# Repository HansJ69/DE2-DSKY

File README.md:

# DE2-DSKY

**8. Apollo DSKY console maquette**: maketa ovládacího rozhraní DSKY z kosmické lodi Apollo.

## O DSKY

**DSKY** (Display and Keyboard) bylo uživatelské rozhraní palubního počítače **Apollo Guidance Computer (AGC)**, vyvinutého v MIT Instrumentation Laboratory. Prostřednictvím DSKY komunikovali astronauti s počítačem během letů na Měsíc.

### Co DSKY umožňovalo

- zadávat příkazy a data do počítače,
- kontrolovat stav lodi,
- počítat korekce dráhy,
- řídit motory,
- provádět astronomickou navigaci.

### Systém VERB a NOUN

Místo textového nebo grafického rozhraní se používal jednoduchý dvojslovný systém:

- **VERB** (sloveso) určuje, *jakou akci* provést,
- **NOUN** (podstatné jméno) určuje, *čeho se akce týká*.

Příklad: `VERB 16 NOUN 36` znamená "průběžně zobrazuj čas počítače".

### Displej a kontrolky

Údaje se zobrazovaly na elektroluminiscenčním displeji, který ukazoval číselné hodnoty ve třech řádcích (registry R1, R2, R3) a kódy programu, VERB a NOUN. Součástí panelu byla také sada stavových kontrolek, například:

- `COMP ACTY` (počítač právě pracuje),
- `PROG` (chyba programu),
- `OPR ERR` (chyba obsluhy),
- `GIMBAL LOCK` (blokace kardanového závěsu).

## O projektu

Cílem projektu je co nejvěrněji napodobit rozhraní **DSKY** z Apolla. Maketa je postavená na **Raspberry Pi Pico** a **vlastní desce plošných spojů (PCB)**.

### Funkce

- Zadávání příkazů systémem **VERB / NOUN** stejně jako v Apolu.
- Několik původních kombinací VERB a NOUN, například zobrazení času.
- Čtení dat z **GPS** a **IMU** přes vlastní VERB/NOUN kódy.
- Vlastní příkazy nad rámec originálu.

### Autentičnost

- **Klávesnice:** mechanické spínače pro odpovídající hmat a zvuk tlačítek.
- **Displej:** místo hotových displejů jsou segmenty tvořeny jednotlivými LED diodami, nad kterými je tvarovaný difuzér. Ten světlo rozptýlí a vytvoří tvar sedmisegmentové číslice. Barva a vzhled se tak co nejvíc blíží původnímu elektroluminiscenčnímu displeji.
- **Kontrolky:** stavové indikátory (původně žárovičky v oknech kontrolek) jsou na panelu ve stejném uspořádání jako na originále.

### Multiplexování

Aby se ušetřily piny Pica, je většina periferií řízena **multiplexně**:

- **Klávesnice** je zapojena jako maticová (řádky a sloupce).
- **LED segmenty displeje** jsou ovládány multiplexem, kdy se jednotlivé číslice rychle střídají.
- **Kontrolky** jsou ve vlastní multiplexní matici.

## Schéma

### Blokové schéma obvodu

## Hardware

### Kusovník (BOM)

| Součástka | Funkce v obvodu | Počet | Odkaz / Datasheet |
| :--- | :--- | :--- | :--- |
| **Raspberry Pi Pico (RP2040)** | Hlavní řídicí mikrokontrolér (skenování matice 5×4, řízení shift registrů, 3× PWM pro jas LED, I2C a UART komunikace) | 1 ks | [Raspberry Pi Pico Datasheet (PDF)](https://datasheets.raspberrypi.com/pico/pico-datasheet.pdf) |
| **SCT2024CSTG** | 16kanálový LED driver (posuvný registr s konstantním proudem a pinem `OE` pro PWM stmívání samostatných větví) | X ks *(min. 3 ks)* | [SCT2024 Datasheet (AllDatasheet)](https://www.alldatasheet.com/view.jsp?Searchword=SCT2024) |
| **Keychron K Pro Switch Mint** | Mechanické spínače pro uživatelskou klávesnici zapojenou v matici 5×4 | 20 ks *(1 balení = 110 ks)* | [Alza – Keychron K Pro Switch Mint](https://www.alza.cz/keychron-k-pro-switch-mint-110-pcs-d12749940.htm) |
| **LED diody (displej, alarmy, tlačítka)** | Optická indikace, segmenty displeje a podsvícení kláves | *k doplnění* | *Doplnit dle konkrétních typů* |
| **Step-down modul s LM2596** | Spínaný snižující DC-DC měnič z 20 V (z PD triggeru) na 5 V pro napájení elektroniky a LED | 2–3 ks *(dle odběru)* | [Drátek – Modul LM2596](https://dratek.cz/arduino-platforma/1303-stepdown-nastavitelny-menic-s-lm2596-dc-dc.html) / [TI LM2596 Datasheet (PDF)](https://www.ti.com/lit/ds/symlink/lm2596.pdf) |
| **USB-C PD Trigger Board (20 V)** | Vyjednání 20V napájecího profilu z powerbanky přes USB-C Power Delivery | 1 ks | [HUSB238 / PD Trigger reference](https://www.alldatasheet.com/view.jsp?Searchword=HUSB238) |
| **QMC5883P (modul)** | 3osý magnetometr (digitální kompas), připojený na sběrnici I2C | 1 ks | [QMC5883P Datasheet (AllDatasheet)](https://www.alldatasheet.com/view.jsp?Searchword=QMC5883P) |
| **MPU-6050 (modul)** | 6osý inerciální senzor (3osý akcelerometr + 3osý gyroskop) na sběrnici I2C | 1 ks | [MPU-6050 Datasheet (TDK InvenSense)](https://invensense.tdk.com/wp-content/uploads/2015/02/MPU-6000-Datasheet1.pdf) |
| **GY-213V-TU21D (čip HTU21D)** | Senzor teploty a relativní vlhkosti na sběrnici I2C | 1 ks | [HTU21D Datasheet (AllDatasheet)](https://www.alldatasheet.com/view.jsp?Searchword=HTU21D) |
| **GY-NEO6MV2 (čip u-blox NEO-6M)** | GPS přijímač komunikující přes TTL sériovou linku (UART) | 1 ks | [u-blox NEO-6 Datasheet (AllDatasheet)](https://www.alldatasheet.com/view.jsp?Searchword=NEO-6M) |

## Software

- Jazyk / platforma: MicroPython
- Knihovny: [doplnit]

## Fotky / ukázka

-

## Zdroje a inspirace

- https://github.com/rrainey/DSKY-digital-indicator-replica/tree/master
- https://github.com/Apollo-Replica/DSKY/tree/main
- https://github.com/ManoDaSilva/AGC_DSKY_Replica

## Tým

|Jméno|GitHub|Role|
|-------|--------|------|
| Adam Šimůnek | [@adamsim10](https://github.com/adamsim10) | - |
| Jan Pikner | [@HansJ69](https://github.com/HansJ69) | - |
| Jan Mareš | [@Error-30](https://github.com/Error-30) | - |

## Struktura repozitáře

```
DE2-DSKY/
├── docs/                         # prostor pro dokumentaci (zatím prázdný)
├── models/                       # prostor pro 3D modely (zatím prázdný)
├── pictures/                     # obrázky a schémata použité v README
│   ├── blok_shem_obvodu.png
│   ├── dsky_interface.png
│   └── dsky_interface_diagram.png
├── pcb/                          # návrhy desek v KiCadu
│   ├── led_display/              # deska LED displeje
│   │   ├── DSKY_led_display.kicad_pro
│   │   ├── DSKY_led_display.kicad_sch
│   │   ├── DSKY_led_display.kicad_pcb
│   │   └── DSKY_led_display.pdf
│   ├── lights_keyboard/          # deska kontrolek a klávesnice
│   │   ├── lights_keyboard.kicad_pro
│   │   ├── lights_keyboard.kicad_sch
│   │   ├── lights_keyboard.kicad_pcb
│   │   ├── buttonmatrix.kicad_sch
│   │   ├── external_connections.kicad_sch
│   │   ├── lights.kicad_sch
│   │   └── Gerber Files/         # výrobní data (Gerbery a vrtání)
│   └── main_board/               # hlavní deska
│       ├── main_board.kicad_pro
│       ├── main_board.kicad_sch
│       └── main_board.kicad_pcb
├── src/                          # prostor pro firmware (zatím prázdný)
│   └── .gitkeep
├── LICENSE
└── README.md
```

V podsložkách s PCB jsou také pomocné soubory KiCadu, knihovny a zálohy návrhů. Výrobní data desky klávesnice jsou uložena také jako archiv `Gerber Files.zip`.

## Stav projektu

- [x] Návrh schématu (PCB)
- [x] Výběr součástek
- [x] Návrh PCB
- [ ] BOM
- [x] Schema zapojení (přibližné)
- [ ] Blokové schéma
- [ ] Dokumentace a fotky

## Licence

Projekt je šířen pod licencí GPL-3.0, viz soubor [LICENSE](LICENSE).

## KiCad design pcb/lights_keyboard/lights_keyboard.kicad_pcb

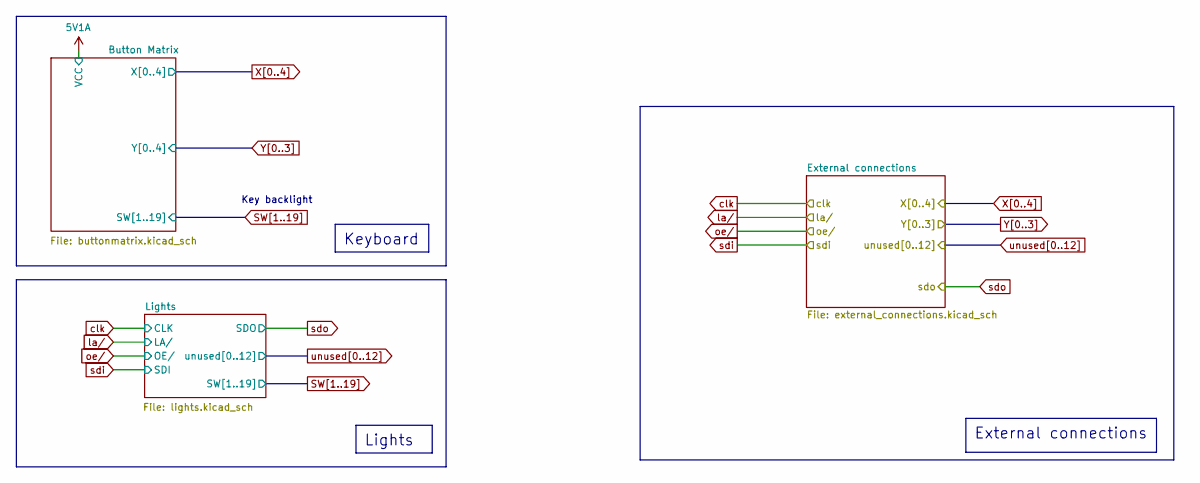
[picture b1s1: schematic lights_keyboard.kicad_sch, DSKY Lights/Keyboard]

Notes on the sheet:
Key backlight
Keyboard
Lights
External connections

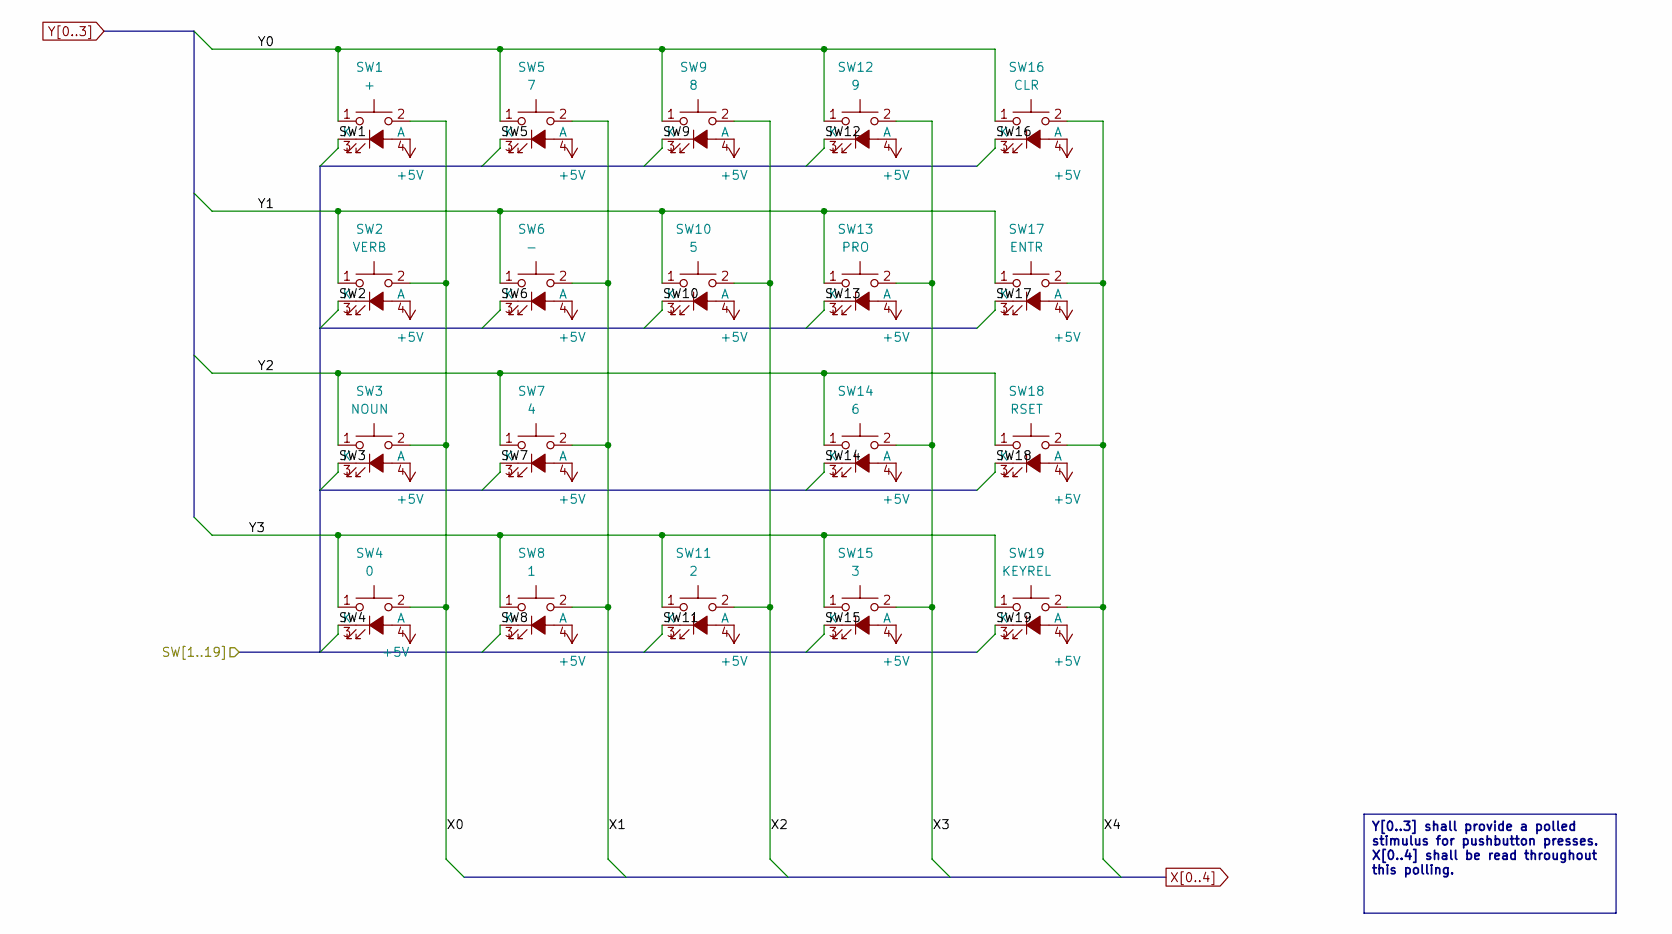
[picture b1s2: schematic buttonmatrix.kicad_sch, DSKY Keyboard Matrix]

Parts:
SW1: +; CherryMX_1.00u_LED
SW2: VERB; CherryMX_1.00u_LED
SW3: NOUN; CherryMX_1.00u_LED
SW4: 0; CherryMX_1.00u_LED
SW5: 7; CherryMX_1.00u_LED
SW6: -; CherryMX_1.00u_LED
SW7: 4; CherryMX_1.00u_LED
SW8: 1; CherryMX_1.00u_LED
SW9: 8; CherryMX_1.00u_LED
SW10: 5; CherryMX_1.00u_LED
SW11: 2; CherryMX_1.00u_LED
SW12: 9; CherryMX_1.00u_LED
SW13: PRO; CherryMX_1.00u_LED
SW14: 6; CherryMX_1.00u_LED
SW15: 3; CherryMX_1.00u_LED
SW16: CLR; CherryMX_1.00u_LED
SW17: ENTR; CherryMX_1.00u_LED
SW18: RSET; CherryMX_1.00u_LED
SW19: KEYREL; CherryMX_1.00u_LED

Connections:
+5V: SW1.4 (A), SW2.4 (A), SW3.4 (A), SW4.4 (A), SW5.4 (A), SW6.4 (A), SW7.4 (A), SW8.4 (A), SW9.4 (A), SW10.4 (A), SW11.4 (A), SW12.4 (A), SW13.4 (A), SW14.4 (A), SW15.4 (A), SW16.4 (A), SW17.4 (A), SW18.4 (A), SW19.4 (A); also elsewhere on the board
SW1: SW1.3 (K); also elsewhere on the board
SW2: SW2.3 (K); also elsewhere on the board
SW3: SW3.3 (K); also elsewhere on the board
SW4: SW4.3 (K); also elsewhere on the board
SW5: SW5.3 (K); also elsewhere on the board
SW6: SW6.3 (K); also elsewhere on the board
SW7: SW7.3 (K); also elsewhere on the board
SW8: SW8.3 (K); also elsewhere on the board
SW9: SW9.3 (K); also elsewhere on the board
SW10: SW10.3 (K); also elsewhere on the board
SW11: SW11.3 (K); also elsewhere on the board
SW12: SW12.3 (K); also elsewhere on the board
SW13: SW13.3 (K); also elsewhere on the board
SW14: SW14.3 (K); also elsewhere on the board
SW15: SW15.3 (K); also elsewhere on the board
SW16: SW16.3 (K); also elsewhere on the board
SW17: SW17.3 (K); also elsewhere on the board
SW18: SW18.3 (K); also elsewhere on the board
SW19: SW19.3 (K); also elsewhere on the board
X0: SW1.2, SW2.2, SW3.2, SW4.2; also elsewhere on the board
X1: SW5.2, SW6.2, SW7.2, SW8.2; also elsewhere on the board
X2: SW9.2, SW10.2, SW11.2; also elsewhere on the board
X3: SW12.2, SW13.2, SW14.2, SW15.2; also elsewhere on the board
X4: SW16.2, SW17.2, SW18.2, SW19.2; also elsewhere on the board
Y0: SW1.1, SW5.1, SW9.1, SW12.1, SW16.1; also elsewhere on the board
Y1: SW2.1, SW6.1, SW10.1, SW13.1, SW17.1; also elsewhere on the board
Y2: SW3.1, SW7.1, SW14.1, SW18.1; also elsewhere on the board
Y3: SW4.1, SW8.1, SW11.1, SW15.1, SW19.1; also elsewhere on the board

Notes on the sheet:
Y[0..3] shall provide a polled stimulus for pushbutton presses. X[0..4] shall be read throughout this polling.

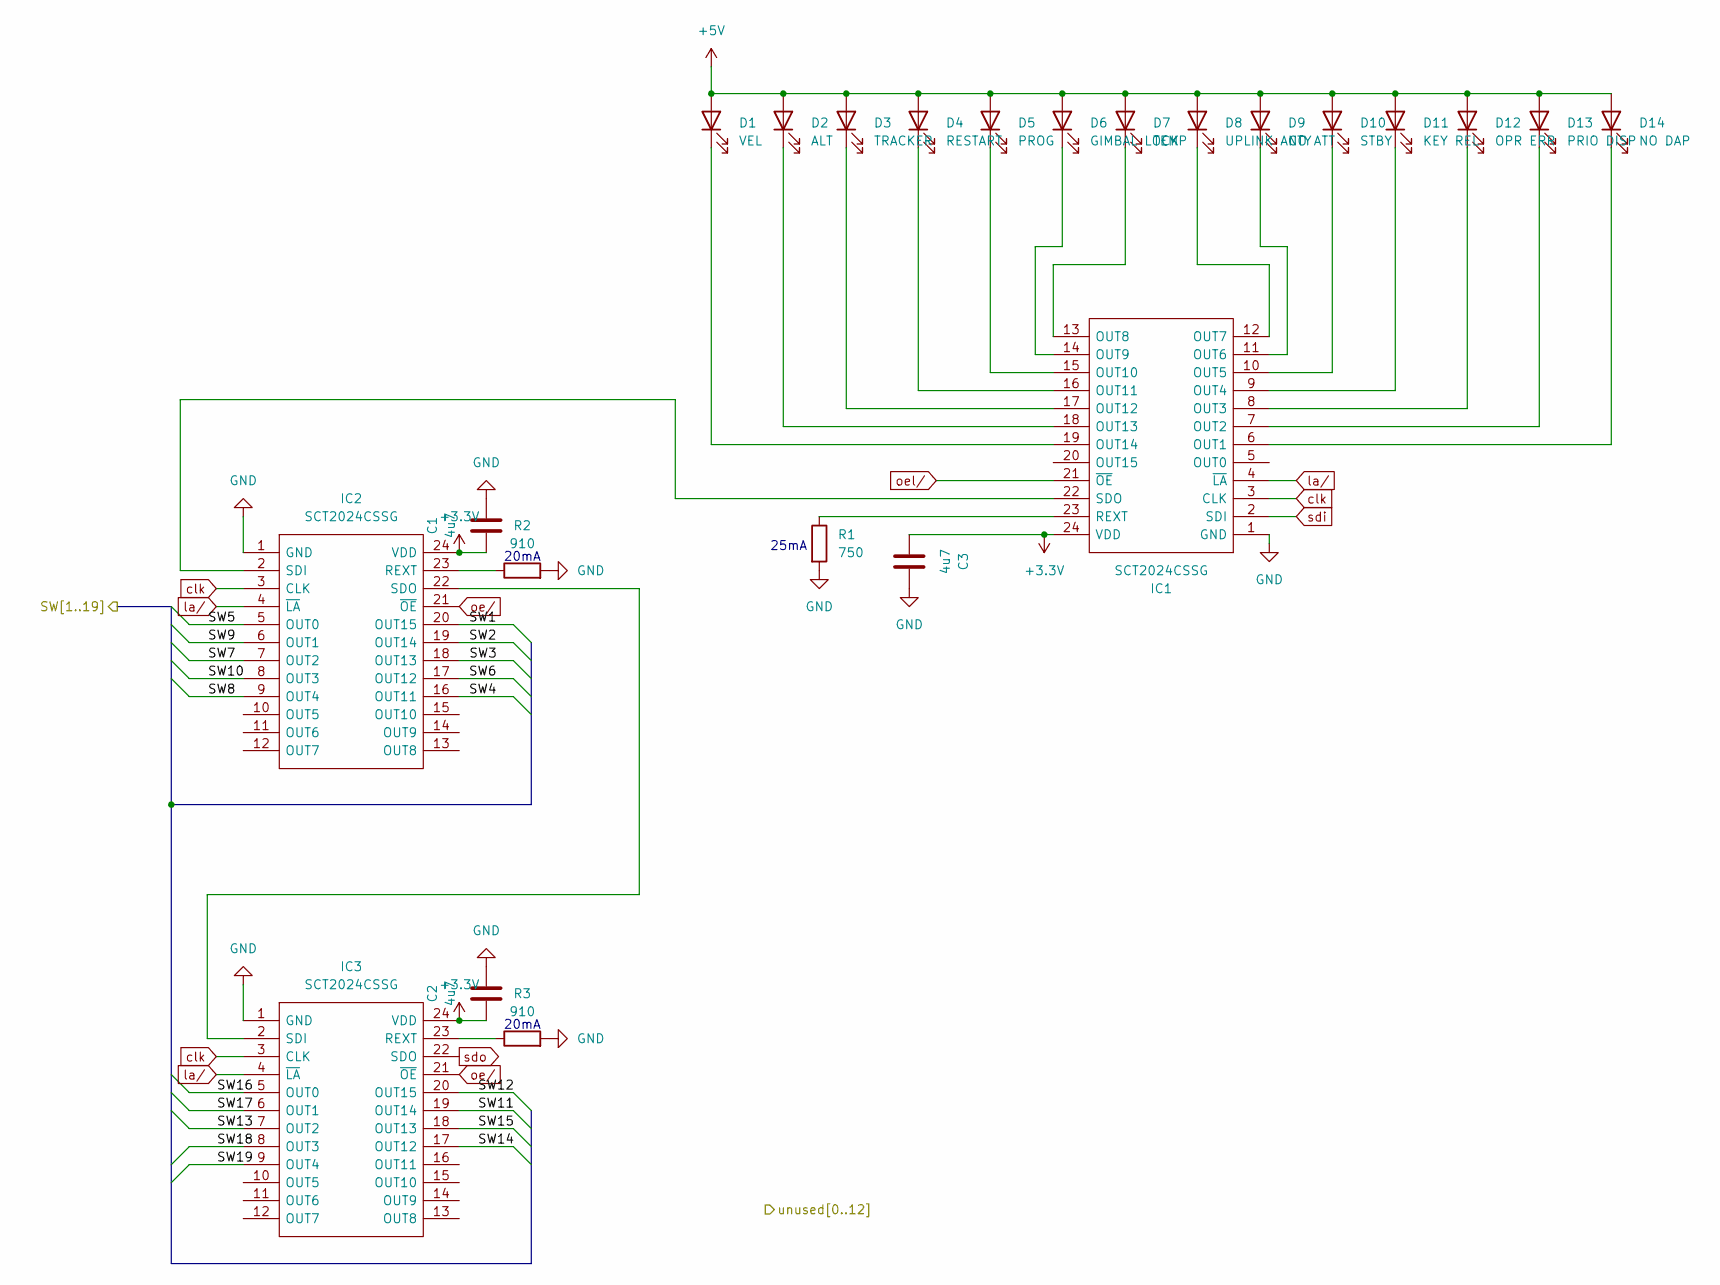
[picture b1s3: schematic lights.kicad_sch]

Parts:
C1, C2, C3: 4u7; LED_0805_2012Metric_Pad1.15x1.40mm_HandSolder
D1: VEL; LED_0805_2012Metric_Pad1.15x1.40mm_HandSolder
D2: ALT; LED_0805_2012Metric_Pad1.15x1.40mm_HandSolder
D3: TRACKER; LED_0805_2012Metric_Pad1.15x1.40mm_HandSolder
D4: RESTART; LED_0805_2012Metric_Pad1.15x1.40mm_HandSolder
D5: PROG; LED_0805_2012Metric_Pad1.15x1.40mm_HandSolder
D6: GIMBAL LOCK; LED_0805_2012Metric_Pad1.15x1.40mm_HandSolder
D7: TEMP; LED_0805_2012Metric_Pad1.15x1.40mm_HandSolder
D8: UPLINK ACTY; LED_0805_2012Metric_Pad1.15x1.40mm_HandSolder
D9: NO ATT; LED_0805_2012Metric_Pad1.15x1.40mm_HandSolder
D10: STBY; LED_0805_2012Metric_Pad1.15x1.40mm_HandSolder
D11: KEY REL; LED_0805_2012Metric_Pad1.15x1.40mm_HandSolder
D12: OPR ERR; LED_0805_2012Metric_Pad1.15x1.40mm_HandSolder
D13: PRIO DISP; LED_0805_2012Metric_Pad1.15x1.40mm_HandSolder
D14: NO DAP; LED_0805_2012Metric_Pad1.15x1.40mm_HandSolder
IC1, IC2, IC3: SCT2024CSSG; SOP64P600X175-24N; Manufacturer_Part_Number SCT2024CSSG
R1: 750; LED_0805_2012Metric_Pad1.15x1.40mm_HandSolder
R2, R3: 910; LED_0805_2012Metric_Pad1.15x1.40mm_HandSolder

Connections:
+3.3V: C1.1, C2.1, C3.1, IC1.24 (VDD), IC2.24 (VDD), IC3.24 (VDD); also elsewhere on the board
+5V: D1.2 (A), D2.2 (A), D3.2 (A), D4.2 (A), D5.2 (A), D6.2 (A), D7.2 (A), D8.2 (A), D9.2 (A), D10.2 (A), D11.2 (A), D12.2 (A), D13.2 (A), D14.2 (A); also elsewhere on the board
GND: C1.2, C2.2, C3.2, IC1.1 (GND), IC2.1 (GND), IC3.1 (GND), R1.2, R2.2, R3.2; also elsewhere on the board
unnamed: D1.1 (K), IC1.19 (OUT14)
unnamed: D2.1 (K), IC1.18 (OUT13)
unnamed: D3.1 (K), IC1.17 (OUT12)
unnamed: D4.1 (K), IC1.16 (OUT11)
unnamed: D5.1 (K), IC1.15 (OUT10)
unnamed: D6.1 (K), IC1.14 (OUT9)
unnamed: D7.1 (K), IC1.13 (OUT8)
unnamed: D8.1 (K), IC1.12 (OUT7)
unnamed: D9.1 (K), IC1.11 (OUT6)
unnamed: D10.1 (K), IC1.10 (OUT5)
unnamed: D11.1 (K), IC1.9 (OUT4)
unnamed: D12.1 (K), IC1.8 (OUT3)
unnamed: D13.1 (K), IC1.7 (OUT2)
unnamed: D14.1 (K), IC1.6 (OUT1)
unnamed: IC1.23 (REXT), R1.1
unnamed: IC1.22 (SDO), IC2.2 (SDI)
unnamed: IC2.23 (REXT), R2.1
unnamed: IC2.22 (SDO), IC3.2 (SDI)
unnamed: IC3.23 (REXT), R3.1
SW1: IC2.20 (OUT15); also elsewhere on the board
SW2: IC2.19 (OUT14); also elsewhere on the board
SW3: IC2.18 (OUT13); also elsewhere on the board
SW4: IC2.16 (OUT11); also elsewhere on the board
SW5: IC2.5 (OUT0); also elsewhere on the board
SW6: IC2.17 (OUT12); also elsewhere on the board
SW7: IC2.7 (OUT2); also elsewhere on the board
SW8: IC2.9 (OUT4); also elsewhere on the board
SW9: IC2.6 (OUT1); also elsewhere on the board
SW10: IC2.8 (OUT3); also elsewhere on the board
SW11: IC3.19 (OUT14); also elsewhere on the board
SW12: IC3.20 (OUT15); also elsewhere on the board
SW13: IC3.7 (OUT2); also elsewhere on the board
SW14: IC3.17 (OUT12); also elsewhere on the board
SW15: IC3.18 (OUT13); also elsewhere on the board
SW16: IC3.5 (OUT0); also elsewhere on the board
SW17: IC3.6 (OUT1); also elsewhere on the board
SW18: IC3.8 (OUT3); also elsewhere on the board
SW19: IC3.9 (OUT4); also elsewhere on the board
clk: IC1.3 (CLK), IC2.3 (CLK), IC3.3 (CLK); also elsewhere on the board
la/: IC1.4 (~LA), IC2.4 (~LA), IC3.4 (~LA); also elsewhere on the board
oel/: IC1.21 (~OE); also elsewhere on the board
oe/: IC2.21 (~OE), IC3.21 (~OE); also elsewhere on the board
sdi: IC1.2 (SDI); also elsewhere on the board
sdo: IC3.22 (SDO); also elsewhere on the board

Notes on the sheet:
25mA
20mA

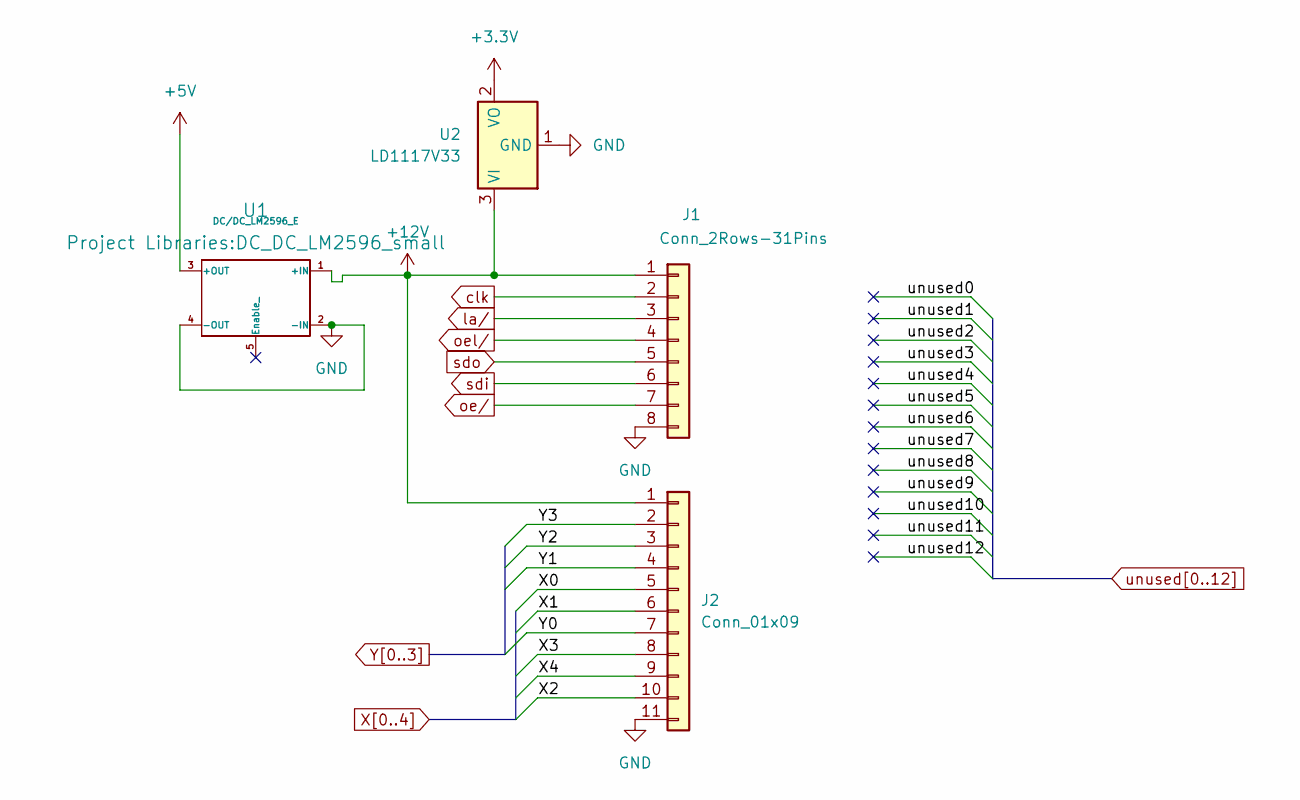
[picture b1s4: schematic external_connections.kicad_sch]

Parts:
J1: Conn_2Rows-31Pins; JST_XH_B8B-XH-A_1x08_P2.50mm_Vertical
J2: Conn_01x09; JST_XH_B11B-XH-A_1x11_P2.50mm_Vertical
U1: DC/DC_LM2596_E; DC_DC_LM2596_small
U2: LD1117V33; TO-220-3_Vertical

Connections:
+3.3V: U2.2 (VO); also elsewhere on the board
+5V: U1.3 (+OUT); also elsewhere on the board
+12V: J1.1, J2.1, U1.1 (+IN), U2.3 (VI)
GND: J1.8, J2.11, U1.2 (-IN), U1.4 (-OUT), U2.1 (GND); also elsewhere on the board
X0: J2.5; also elsewhere on the board
X1: J2.6; also elsewhere on the board
X2: J2.10; also elsewhere on the board
X3: J2.8; also elsewhere on the board
X4: J2.9; also elsewhere on the board
Y0: J2.7; also elsewhere on the board
Y1: J2.4; also elsewhere on the board
Y2: J2.3; also elsewhere on the board
Y3: J2.2; also elsewhere on the board
clk: J1.2; also elsewhere on the board
la/: J1.3; also elsewhere on the board
oel/: J1.4; also elsewhere on the board
oe/: J1.7; also elsewhere on the board
sdi: J1.6; also elsewhere on the board
sdo: J1.5; also elsewhere on the board

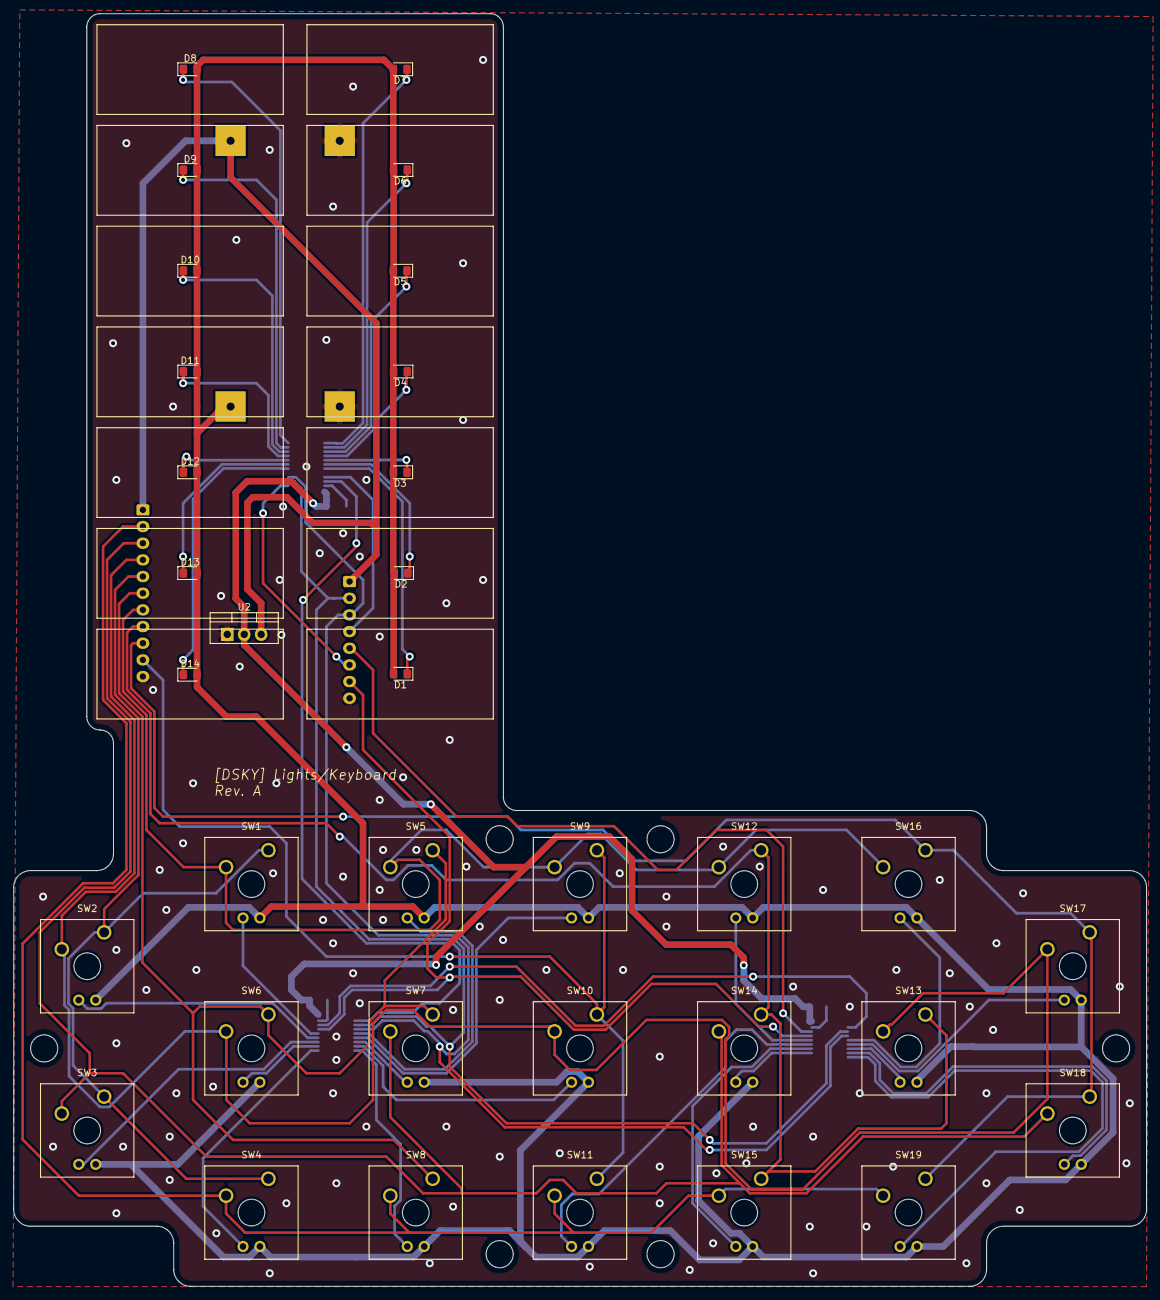
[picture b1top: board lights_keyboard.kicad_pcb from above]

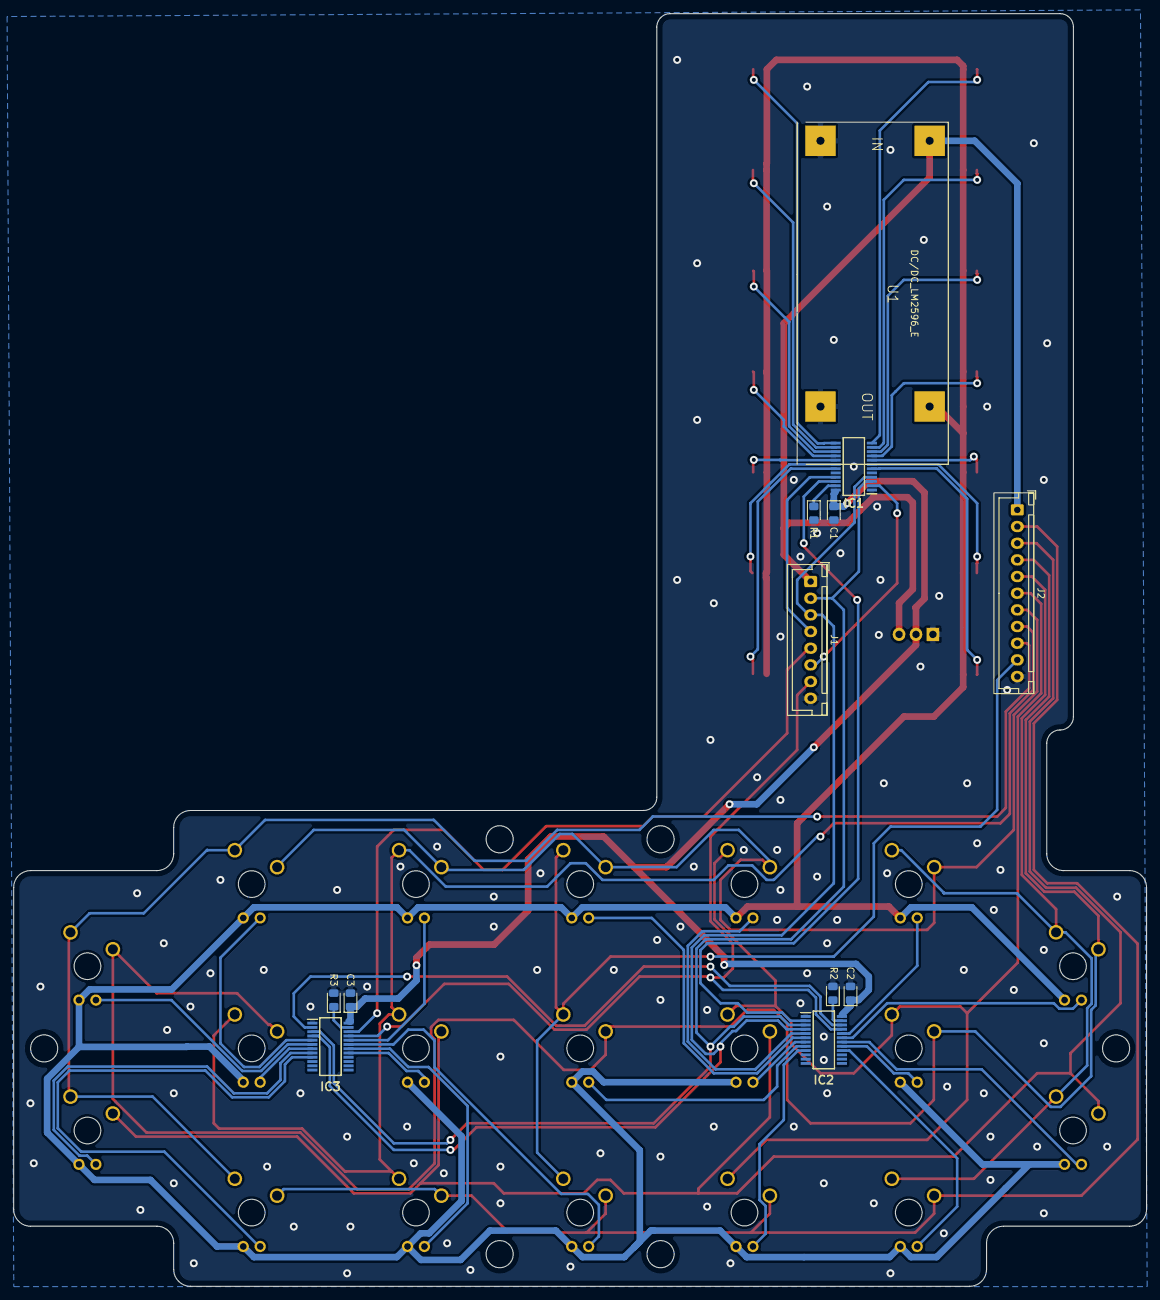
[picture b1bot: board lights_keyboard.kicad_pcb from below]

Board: 2 copper layers, 169.9 x 190.9 mm, 46 parts (12 on the bottom side), 57 nets.

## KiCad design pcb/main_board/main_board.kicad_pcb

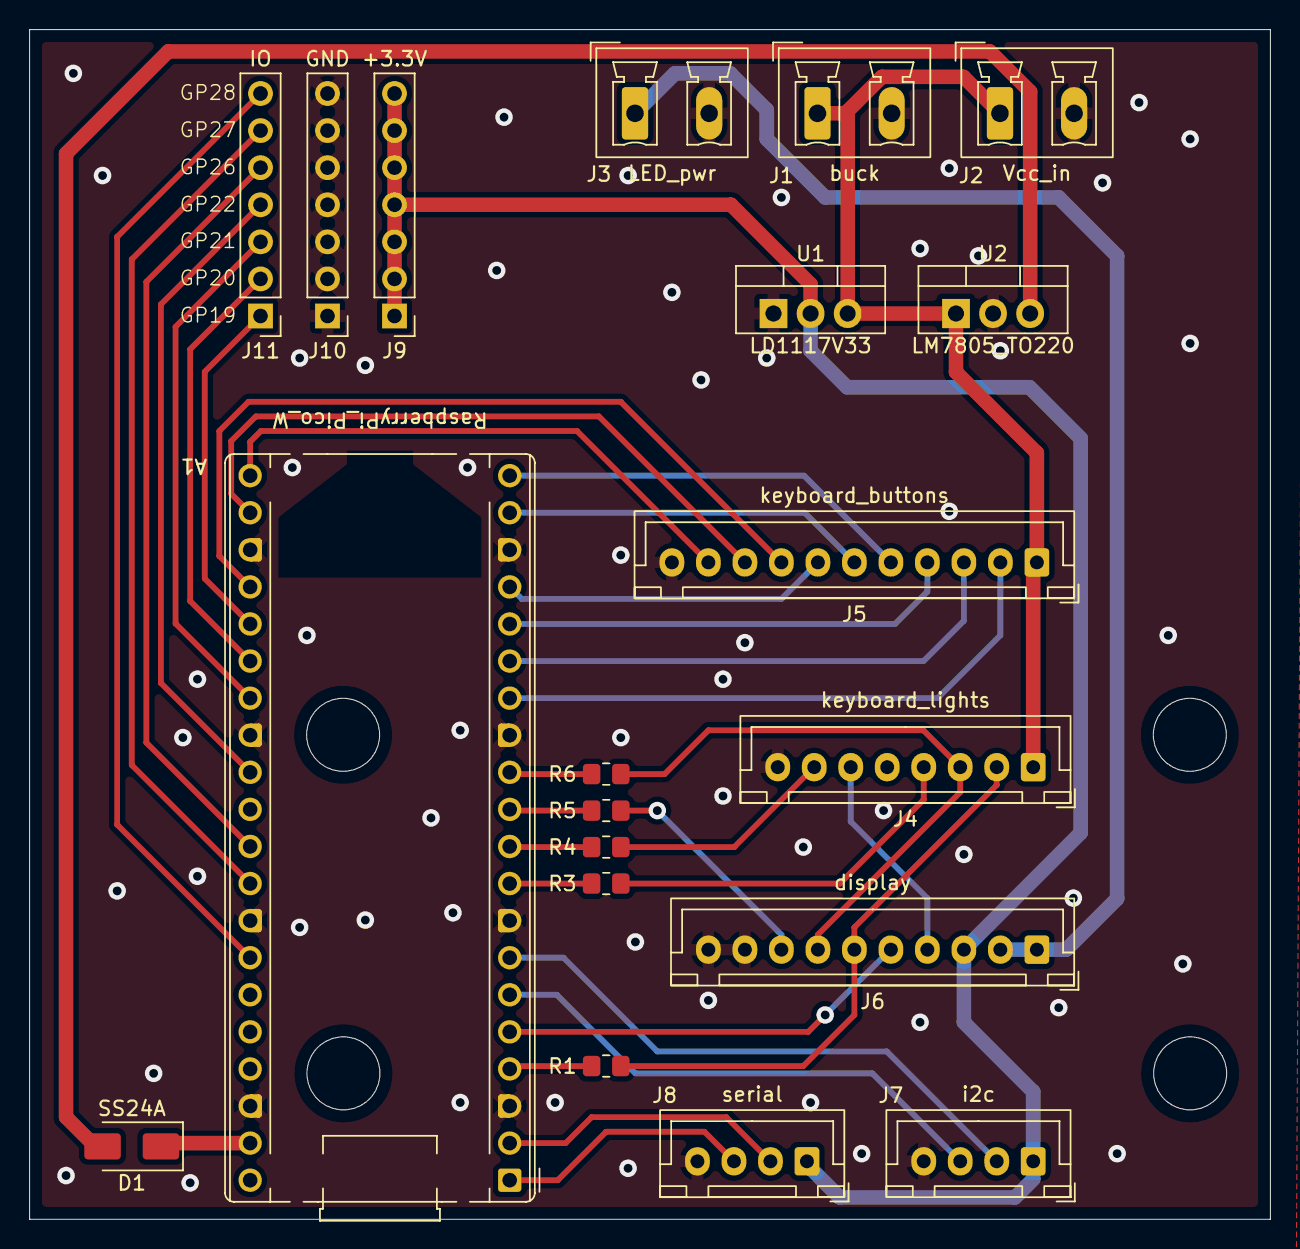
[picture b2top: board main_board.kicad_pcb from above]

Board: 2 copper layers, 85.0 x 81.5 mm, 20 parts (0 on the bottom side), 38 nets.

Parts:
A1: RaspberryPi_Pico_W; RaspberryPi_Pico_Common_THT
D1: SS24A; D_SMA
J1: buck; PhoenixContact_MCV_1,5_2-G-5.08_1x02_P5.08mm_Vertical
J2: Vcc_in; PhoenixContact_MCV_1,5_2-G-5.08_1x02_P5.08mm_Vertical
J3: LED_pwr; PhoenixContact_MCV_1,5_2-G-5.08_1x02_P5.08mm_Vertical
J4: keyboard_lights; JST_XH_B8B-XH-A_1x08_P2.50mm_Vertical
J5: keyboard_buttons; JST_XH_B11B-XH-A_1x11_P2.50mm_Vertical
J6: display; JST_XH_B10B-XH-A_1x10_P2.50mm_Vertical
J7: i2c; JST_XH_B4B-XH-A_1x04_P2.50mm_Vertical
J8: serial; JST_XH_B4B-XH-A_1x04_P2.50mm_Vertical
J9: +3.3V; PinHeader_1x07_P2.54mm_Vertical
J10: GND; PinHeader_1x07_P2.54mm_Vertical
J11: IO; PinHeader_1x07_P2.54mm_Vertical
R1, R3, R4, R5, R6: 33; R_0805_2012Metric_Pad1.20x1.40mm_HandSolder
U1: LD1117V33; TO-220-3_Vertical
U2: LM7805_TO220; TO-220-3_Vertical

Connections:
+3.3V: J6.3, J7.1, J8.1, J9.1, J9.2, J9.3, J9.4, J9.5, J9.6, J9.7, U1.2 (VO)
+5V: D1.2 (A), U2.3 (VO)
+12V: J1.1, J2.1, J4.1, J5.1, U1.3 (VI), U2.1 (VI)
GND: A1.3 (GND), A1.8 (GND), A1.13 (GND), A1.18 (GND), A1.23 (GND), A1.28 (GND), A1.33 (AGND), A1.38 (GND), J1.2, J2.2, J3.2, J4.8, J5.11, J6.9, J6.10, J7.4, J8.4, J10.1, J10.2, J10.3, J10.4, J10.5, J10.6, J10.7, U1.1 (GND), U2.2 (GND)
unnamed: A1.4 (GPIO2), R1.2
unnamed: A1.9 (GPIO6), R3.2
unnamed: A1.10 (GPIO7), R4.2
unnamed: A1.11 (GPIO8), R5.2
unnamed: A1.12 (GPIO9), R6.2
unnamed: A1.25 (GPIO19), J11.1
unnamed: A1.26 (GPIO20), J11.2
unnamed: A1.27 (GPIO21), J11.3
unnamed: A1.29 (GPIO22), J11.4
unnamed: A1.31 (GPIO26_ADC0), J11.5
unnamed: A1.32 (GPIO27_ADC1), J11.6
unnamed: A1.34 (GPIO28_ADC2), J11.7
unnamed: A1.39 (VSYS), D1.1 (K)
RX: A1.2 (GPIO1), J8.2
TX: A1.1 (GPIO0), J8.3
V_led: J3.1, J6.1, J6.2
X0: A1.20 (GPIO15), J5.5
X1: A1.19 (GPIO14), J5.6
X2: A1.21 (GPIO16), J5.10
X3: A1.24 (GPIO18), J5.8
X4: A1.22 (GPIO17), J5.9
Y0: A1.17 (GPIO13), J5.7
Y1: A1.16 (GPIO12), J5.4
Y2: A1.15 (GPIO11), J5.3
Y3: A1.14 (GPIO10), J5.2
clk: J4.2, J6.6, R1.1
la: J4.3, J6.7, R6.1
oe_alarm: J4.7, R4.1
oe_display: J6.8, R5.1
oe_keyboard: J4.4, R3.1
scl: A1.7 (GPIO5), J7.2
sda: A1.6 (GPIO4), J7.3
sdi_display: A1.5 (GPIO3), J6.5
sdi_keyboard: J4.6, J6.4
